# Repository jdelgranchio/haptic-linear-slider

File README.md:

# Haptic Linear Slider

A PCB for a motorized, haptic linear slider. An RP2354 (RP2350 with built-in flash) drives a
Bourns PSM01 motorized slide potentiometer through a DRV8876 H-bridge. The board also has a
14 V boost (TLV61048) for the motor supply, a buck converter (DIO54335), USB-C, and SWD over
Tag-Connect TC2030.

Made with **KiCad 10**.

## Layout

```
haptic-linear-slider.kicad_{pro,sch,pcb}
sym-lib-table, fp-lib-table       project library tables (paths use ${KIPRJMOD})
lib/
  _symbols/
    haptic-linear-slider.kicad_sym   project symbols, library nickname "_Symbols"
    MCU_RaspberryPi_RP2350.kicad_sym RP2350 symbol from Raspberry Pi's minimal design
  _footprints.pretty/                project footprints, library nickname "_Footprints"
  _3D/                               STEP models for project footprints
scripts/export.sh                    generates fab outputs and docs with kicad-cli
scripts/site.sh                      builds the GitHub Pages index from those outputs
.github/workflows/kicad.yml          CI: export, Pages (main), releases (v* tags)
```

Use the stock KiCad libraries for anything they already cover. Add a part to the project
libraries only when they don't have it.

## Adding a part from Mouser

1. Download the KiCad model from the Mouser product page (SamacSys / Library Loader).
2. In the Symbol Editor, copy the symbol into `_Symbols`. Rename it to
   `<short description> (<manufacturer>)`, e.g. `37V 3.5A H-Bridge (Texas Instruments)`.
3. Copy the `.kicad_mod` into `lib/_footprints.pretty/` and the `.stp` into `lib/_3D/`.
4. Set the footprint's 3D model to `${KIPRJMOD}/lib/_3D/<part>.stp`. Set the symbol's
   `Footprint` field to `_Footprints:<name>`.
5. Keep the `Manufacturer_Name`, `Manufacturer_Part_Number`, `Mouser Part Number` and
   `Mouser Price/Stock` fields. The BOM export reads them.

## Generating outputs

```sh
scripts/export.sh                 # writes everything to output/ (git-ignored)
STRICT_ERC=1 scripts/export.sh    # fail on ERC violations (STRICT_DRC=1, or STRICT=1 for both)
IBOM=path/to/generate_interactive_bom.py scripts/export.sh   # also build the interactive BOM
```

This produces:

- **checks**: ERC/DRC reports
- **fab**: Gerbers and drill files (plus a zip), a grouped BOM with part-number columns, a
  pick-and-place CSV
- **docs**: schematic PDF, PCB layers PDF, top/bottom assembly drawing PDFs, top/bottom 3D
  renders (PNG), a 3D STEP model
- **presentation**: board outline SVGs, bare and with part bodies, for slides and handbooks
- **datasheets**: a PDF per BOM part, from the `Datasheet` field. Some hosts (Mouser,
  Samsung, ST, …) block scripted downloads. Save those by hand as
  `lib/datasheets/<MPN>.pdf`; the CI run summary lists which ones are missing.

The Gerber layers come from the plot settings saved in the board file (PCB Editor → Plot).
Title blocks show `${REVISION}`: "dev" in the editor, the git tag or short SHA in exports.

## CI

- **Push to `main`**: builds everything, fails on ERC violations, and publishes the latest
  outputs to GitHub Pages. Only the newest deploy is kept. Per-commit workflow artifacts
  expire after 14 days.
- **Push a `v*` tag** (e.g. `v0.1`): also attaches all outputs to a GitHub release. Tag each
  revision you send to fab.

CI uses the `kicad/kicad:10.0-full` image (it includes the stock 3D models). DRC is report-only for now. Set `STRICT_DRC: 1` in the workflow once routing is done.

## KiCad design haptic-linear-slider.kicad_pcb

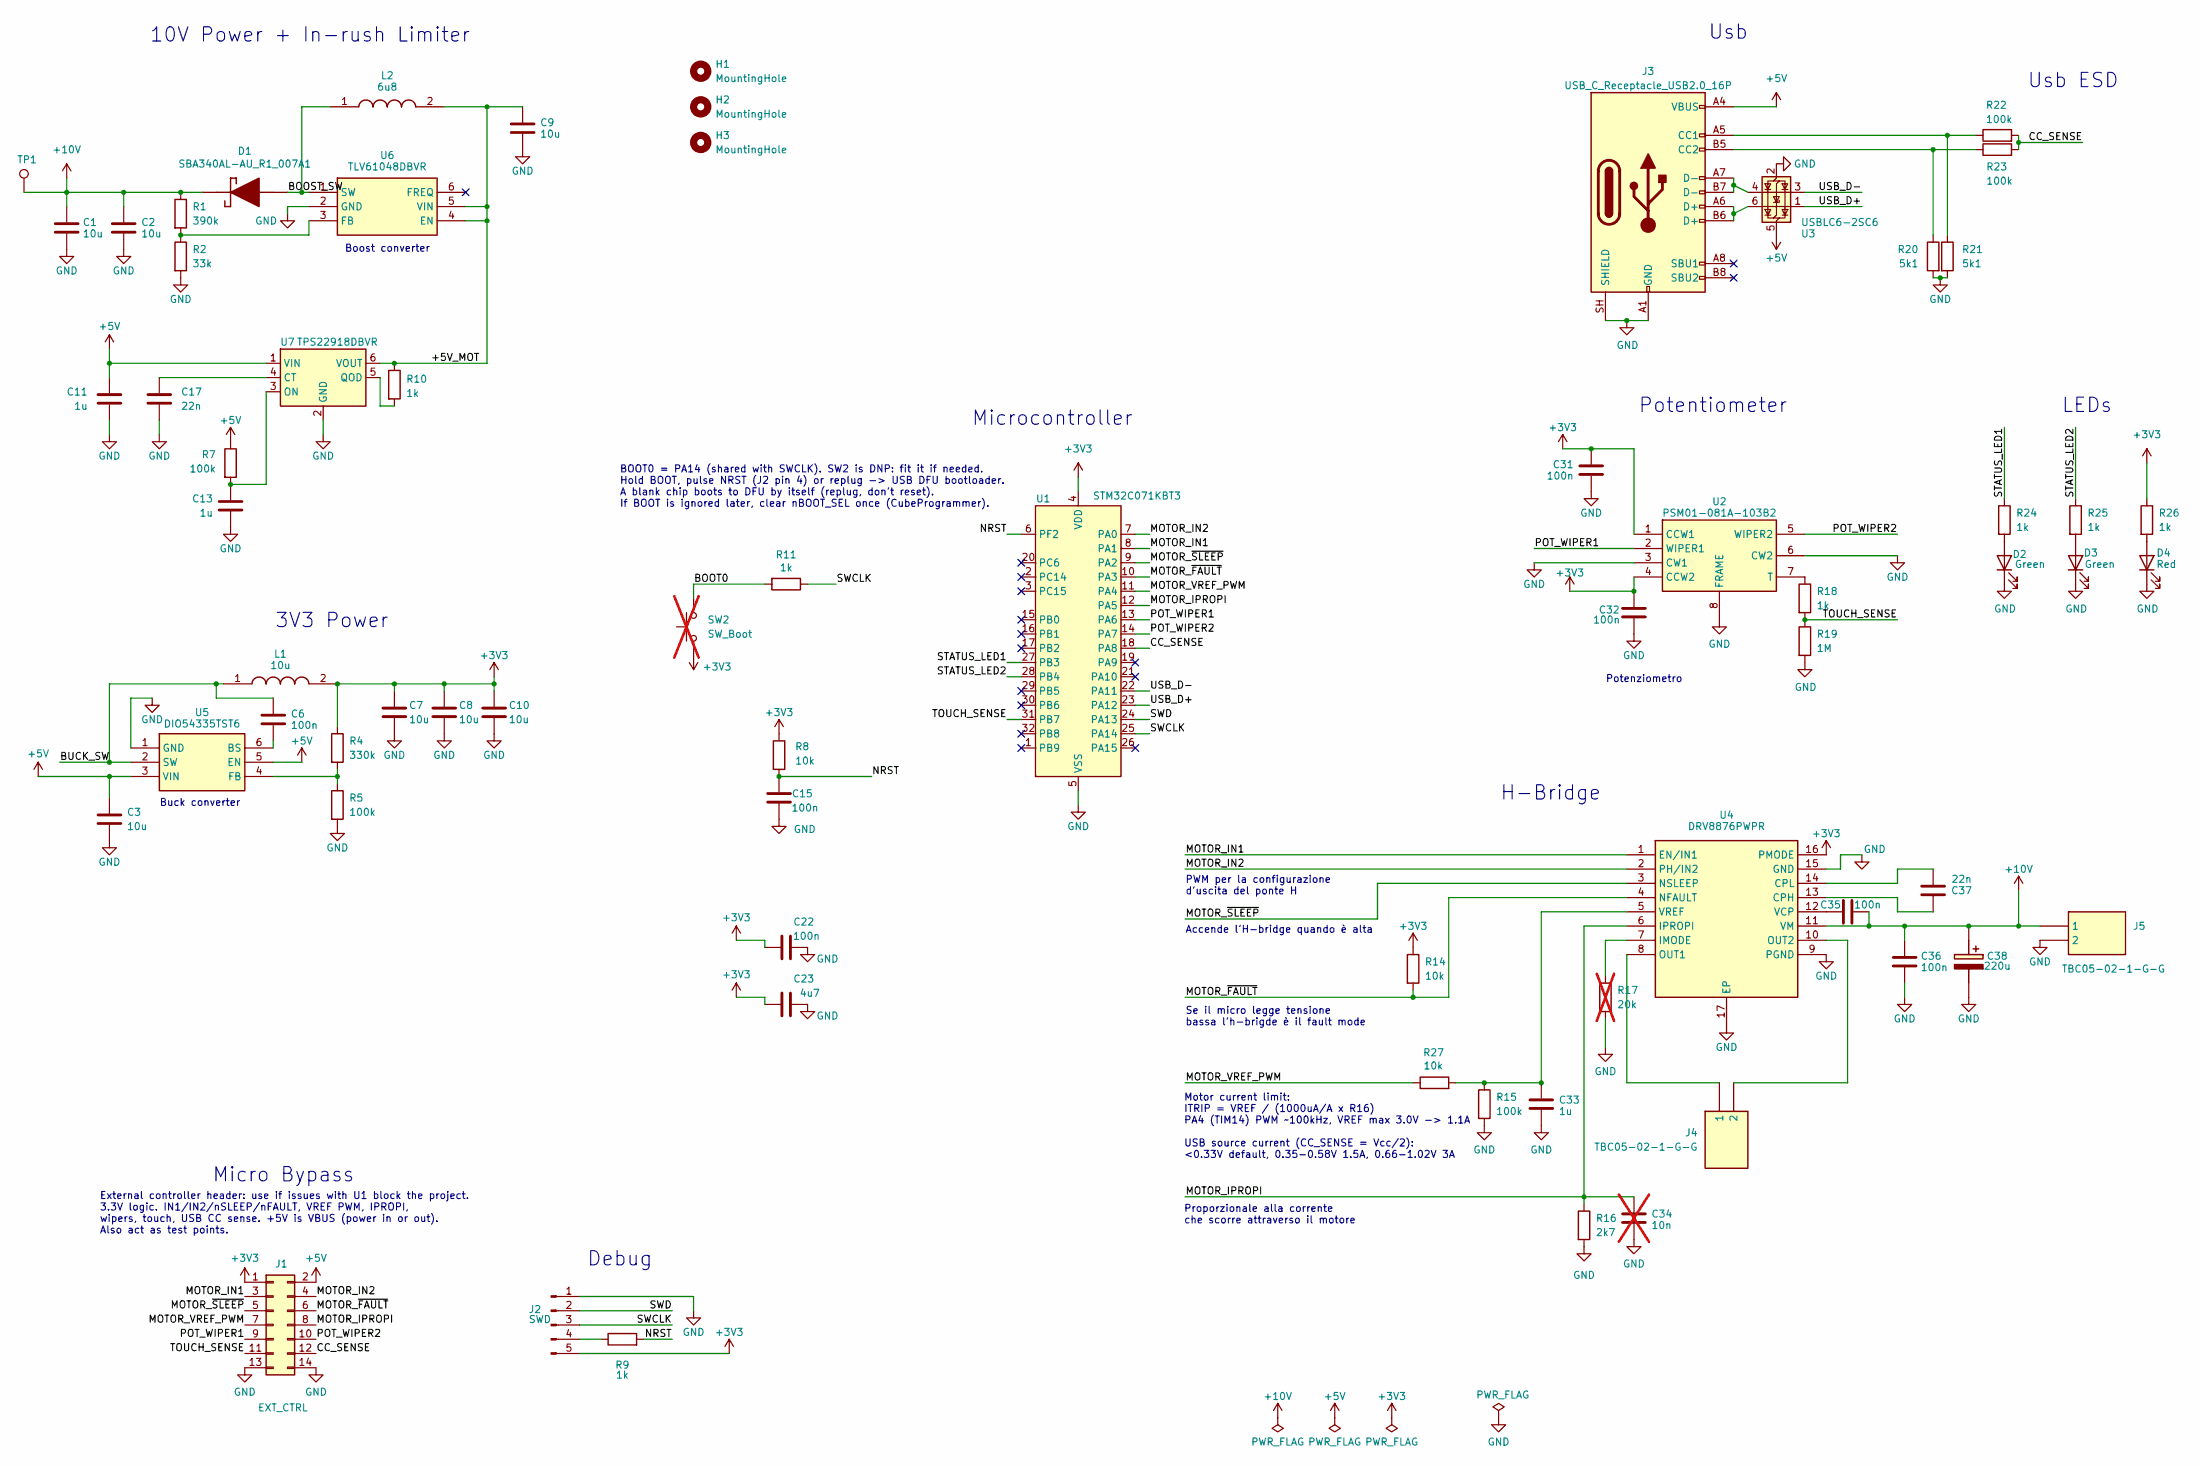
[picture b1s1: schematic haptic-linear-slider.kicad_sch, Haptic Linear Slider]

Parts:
C1, C2, C3, C7, C8, C9, C10: 10u; C_1210_3225Metric_Pad1.33x2.70mm_HandSolder; Manufacturer_Part_Number CL32B106KBJNNWE; Mouser Part Number 187-CL32B106KBJNNWE
C6, C15, C22, C31, C32, C35, C36: 100n; C_0805_2012Metric_Pad1.18x1.45mm_HandSolder; Mouser Part Number 187-CL21B104KBCNNNC
C11, C13: 1u; C_0805_2012Metric_Pad1.18x1.45mm_HandSolder; Mouser Part Number 187-CL21B105KBFNNNG
C17, C37: 22n; C_0805_2012Metric_Pad1.18x1.45mm_HandSolder; Mouser Part Number 187-CL21B223KBANNNC
C23: 4u7; C_0805_2012Metric_Pad1.18x1.45mm_HandSolder; Mouser Part Number 187-CL21A475KAQNNNE
C33: 1u; C_0805_2012Metric_Pad1.18x1.45mm_HandSolder; Manufacturer_Part_Number CL21B105KBFNNNG; Mouser Part Number 187-CL21B105KBFNNNG
C34: 10n; C_0805_2012Metric_Pad1.18x1.45mm_HandSolder; Manufacturer_Part_Number CL21B103KBANNNC; Mouser Part Number 187-CL21B103KBANNNC; not fitted
C38: 220u; CAPPRD350W52D800H1300; Manufacturer_Part_Number 860020574012; Mouser Part Number 710-860020574012
D1: SBA340AL-AU_R1_007A1; SODFL3618X110N; Mouser Part Number 241-SBA340AL-AUR17A1
D2, D3: Green; LED_0805_2012Metric_Pad1.15x1.40mm_HandSolder; Manufacturer_Part_Number 150080VS75000; Mouser Part Number 710-150080VS75000
D4: Red; LED_0805_2012Metric_Pad1.15x1.40mm_HandSolder; Manufacturer_Part_Number 150080RS75000; Mouser Part Number 710-150080RS75000
H1, H2, H3: MountingHole; MountingHole_3.2mm_M3
J1: EXT_CTRL; PinHeader_2x07_P2.54mm_Vertical; Manufacturer_Part_Number 61301421121; Mouser Part Number 710-61301421121
J2: SWD; PinHeader_1x05_P2.54mm_Vertical; Manufacturer_Part_Number 61300511121; Mouser Part Number 710-61300511121
J3: USB_C_Receptacle_USB2.0_16P; USB_C_Receptacle_GCT_USB4105-xx-A_16P_TopMnt_Horizontal; Manufacturer_Part_Number USB4105-GF-A; Mouser Part Number 640-USB4105-GF-A
J4, J5: TBC05-02-1-G-G; TBC05021GG; Mouser Part Number 640-TBC05-02-1-G-G
L1: 10u; AMRM00101040100MA1; Mouser Part Number 673-AMRM101040100MA1
L2: 6u8; MPLSE60406R8; Mouser Part Number 946-MPL-SE6040-6R8
R1: 390k; R_0805_2012Metric_Pad1.20x1.40mm_HandSolder; Manufacturer_Part_Number RC0805FR-07390KL; Mouser Part Number 603-RC0805FR-07390KL
R2: 33k; R_0805_2012Metric_Pad1.20x1.40mm_HandSolder; Manufacturer_Part_Number RC0805FR-0733KL; Mouser Part Number 603-RC0805FR-0733KL
R4: 330k; R_0805_2012Metric_Pad1.20x1.40mm_HandSolder; Manufacturer_Part_Number RC0805FR-07330KL; Mouser Part Number 603-RC0805FR-07330KL
R5, R7, R15, R22, R23: 100k; R_0805_2012Metric_Pad1.20x1.40mm_HandSolder; Manufacturer_Part_Number RC0805FR-07100KL; Mouser Part Number 603-RC0805FR-07100KL
R8, R14, R27: 10k; R_0805_2012Metric_Pad1.20x1.40mm_HandSolder; Manufacturer_Part_Number RC0805FR-0710KL; Mouser Part Number 603-RC0805FR-0710KL
R9, R10, R11, R18, R24, R25, R26: 1k; R_0805_2012Metric_Pad1.20x1.40mm_HandSolder; Manufacturer_Part_Number RC0805FR-071KL; Mouser Part Number 603-RC0805FR-071KL
R16: 2k7; R_0805_2012Metric_Pad1.20x1.40mm_HandSolder; Manufacturer_Part_Number RC0805FR-072K7L; Mouser Part Number 603-RC0805FR-072K7L
R17: 20k; R_0805_2012Metric_Pad1.20x1.40mm_HandSolder; Manufacturer_Part_Number RC0805FR-0720KL; Mouser Part Number 603-RC0805FR-0720KL; not fitted
R19: 1M; R_0805_2012Metric_Pad1.20x1.40mm_HandSolder; Manufacturer_Part_Number RC0805FR-071ML; Mouser Part Number 603-RC0805FR-071ML
R20, R21: 5k1; R_0805_2012Metric_Pad1.20x1.40mm_HandSolder; Manufacturer_Part_Number RC0805FR-075K1L; Mouser Part Number 603-RC0805FR-075K1L
SW2: SW_Boot; 434133025816; Manufacturer_Part_Number 434133025816; Mouser Part Number 710-434133025816; not fitted
TP1: TestPoint; TestPoint_THTPad_D1.0mm_Drill0.5mm
U1: STM32C071KBT3; LQFP-32_7x7mm_P0.8mm; Manufacturer_Part_Number STM32C071KBT3; Mouser Part Number 511-STM32C071KBT3
U2: PSM01-081A-103B2; PSM01081A103B2; Mouser Part Number 652-PSM01081A103B2
U3: USBLC6-2SC6; Manufacturer_Part_Number USBLC6-2SC6; Mouser Part Number 511-USBLC6-2SC6
U4: DRV8876PWPR; SOP65P640X120-17N; Mouser Part Number 595-DRV8876PWPR
U5: DIO54335TST6; SOT95P280X90-6N; Mouser Part Number 453-DIO54335TST6
U6: TLV61048DBVR; SOT95P280X145-6N; Mouser Part Number 595-TLV61048DBVR
U7: TPS22918DBVR; SOT-23-6; Manufacturer_Part_Number TPS22918DBVR; Mouser Part Number 595-TPS22918DBVR

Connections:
+3V3: C7.1, C8.1, C10.1, C22.1, C23.1, C31.1, C32.1, J1.1, J2.5, L1.2, R4.1, R8.1, R14.1, R26.1, SW2.1, U1.4 (VDD), U2.1 (CCW1), U2.4 (CCW2), U4.16 (PMODE)
+5V: C3.1, C11.1, J1.2, J3.A4 (VBUS), J3.A9 (VBUS), J3.B4 (VBUS), J3.B9 (VBUS), R7.1, U3.5 (VBUS), U5.3 (VIN), U5.5 (EN), U7.1 (VIN)
+10V: C1.1, C2.1, C35.2, C36.1, C38.1 (+), D1.1 (K), J5.1, R1.1, TP1.1 (1_1), U4.11 (VM)
/+5V_MOT: C9.1, L2.2, R10.1, U6.4 (EN), U6.5 (VIN), U7.6 (VOUT)
/BOOST_SW: D1.2 (A), L2.1, U6.1 (SW)
/BOOT0: R11.2, SW2.2
/BUCK_SW: C6.1, L1.1, U5.2 (SW)
/CC_SENSE: J1.12, R22.2, R23.2, U1.18 (PA8)
/MOTOR_IN1: J1.3, U1.8 (PA1), U4.1 (EN/IN1)
/MOTOR_IN2: J1.4, U1.7 (PA0), U4.2 (PH/IN2)
/MOTOR_IPROPI: C34.1, J1.8, R16.1, U1.12 (PA5), U4.6 (IPROPI)
/MOTOR_VREF_PWM: J1.7, R27.1, U1.11 (PA4)
/MOTOR_~FAULT: J1.6, R14.2, U1.10 (PA3), U4.4 (NFAULT)
/MOTOR_~SLEEP: J1.5, U1.9 (PA2), U4.3 (NSLEEP)
/NRST: C15.2, R8.2, R9.2, U1.6 (PF2)
/POT_WIPER1: J1.9, U1.13 (PA6), U2.2 (WIPER1)
/POT_WIPER2: J1.10, U1.14 (PA7), U2.5 (WIPER2)
/STATUS_LED1: R24.1, U1.27 (PB3)
/STATUS_LED2: R25.1, U1.28 (PB4)
/SWCLK: J2.3, R11.1, U1.25 (PA14)
/SWD: J2.2, U1.24 (PA13)
/TOUCH_SENSE: J1.11, R18.2, R19.1, U1.31 (PB7)
/USB_D+: U1.23 (PA12), U3.1 (I/O1)
/USB_D-: U1.22 (PA11), U3.3 (I/O2)
GND: C1.2, C2.2, C3.2, C7.2, C8.2, C9.2, C10.2, C11.2, C13.2, C15.1, C17.2, C22.2, C23.2, C31.2, C32.2, C33.2, C34.2, C36.2, C38.2 (-), D2.1 (K), D3.1 (K), D4.1 (K), J1.13, J1.14, J2.1, J3.A1 (GND), J3.A12 (GND), J3.B1 (GND), J3.B12 (GND), J3.SH (SHIELD), J5.2, R2.2, R5.2, R15.2, R16.2, R17.2, R19.2, R20.2, R21.2, U1.5 (VSS), U2.3 (CW1), U2.6 (CW2), U2.8 (FRAME), U2.9 (FRAME), U3.2 (GND), U4.9 (PGND), U4.15 (GND), U4.17 (EP), U5.1 (GND), U6.2 (GND), U7.2 (GND)
unnamed: D2.2 (A), R24.2
unnamed: D3.2 (A), R25.2
unnamed: D4.2 (A), R26.2
unnamed: J2.4, R9.1
unnamed: J3.A5 (CC1), R21.1, R22.1
unnamed: J3.B5 (CC2), R20.1, R23.1
unnamed: J3.A6 (D+), J3.B6 (D+), U3.6 (I/O1)
unnamed: J3.A7 (D-), J3.B7 (D-), U3.4 (I/O2)
unnamed: R18.1, U2.7 (T)
unnamed: C37.1, U4.13 (CPH)
unnamed: C37.2, U4.14 (CPL)
unnamed: R17.1, U4.7 (IMODE)
unnamed: J4.1, U4.8 (OUT1)
unnamed: J4.2, U4.10 (OUT2)
unnamed: C35.1, U4.12 (VCP)
unnamed: C33.1, R15.1, R27.2, U4.5 (VREF)
unnamed: C6.2, U5.6 (BS)
unnamed: R4.2, R5.1, U5.4 (FB)
unnamed: R1.2, R2.1, U6.3 (FB)
unnamed: C17.1, U7.4 (CT)
unnamed: C13.1, R7.2, U7.3 (ON)
unnamed: R10.2, U7.5 (QOD)

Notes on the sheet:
Micro Bypass
Proporzionale alla corrente che scorre attraverso il motore
Usb ESD
Potenziometro
Se il micro legge tensione bassa l'h-brigde è il fault mode
Boost converter
H-Bridge
BOOT0 = PA14 (shared with SWCLK). SW2 is DNP: fit it if needed. Hold BOOT, pulse NRST (J2 pin 4) or replug -> USB DFU bootloader. A blank chip boots to DFU by itself (replug, don't reset). If BOOT is ignored later, clear nBOOT_SEL once (CubeProgrammer).
Usb
Motor current limit: ITRIP = VREF / (1000uA/A x R16) PA4 (TIM14) PWM ~100kHz, VREF max 3.0V -> 1.1A USB source current (CC_SENSE = Vcc/2): <0.33V default, 0.35-0.58V 1.5A, 0.66-1.02V 3A
10V Power + In-rush Limiter
Buck converter
Accende l'H-bridge quando è alta
3V3 Power
Microcontroller
External controller header: use if issues with U1 block the project. 3.3V logic. IN1/IN2/nSLEEP/nFAULT, VREF PWM, IPROPI, wipers, touch, USB CC sense. +5V is VBUS (power in or out). Also act as test points.
Debug
Potentiometer
PWM per la configurazione d'uscita del ponte H
LEDs

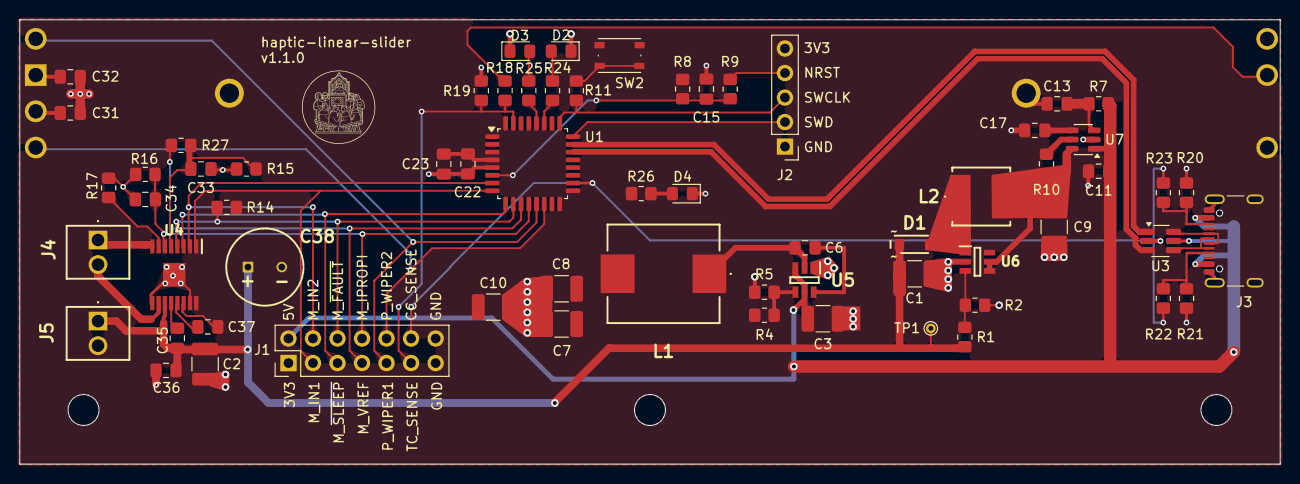
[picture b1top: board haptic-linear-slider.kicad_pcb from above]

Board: 2 copper layers, 130.5 x 46.0 mm, 68 parts (1 on the bottom side), 47 nets.

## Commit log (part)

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2026-04-24 cleaned up symbols
2026-04-24 cleaned up footprints
2026-04-24 3D models are mostly working
2026-04-25 testo spostato
2026-04-25 Test
